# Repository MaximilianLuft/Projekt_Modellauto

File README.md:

# Institutsprojekt 4. Semester #
## Aufbau eines elektrischen Modellautos ##

## FAQ

### What KiCad version to use?
The used template projects are created with KiCad 9.0

### Where to get KiCad?

[kicad.org](https://www.kicad.org/)

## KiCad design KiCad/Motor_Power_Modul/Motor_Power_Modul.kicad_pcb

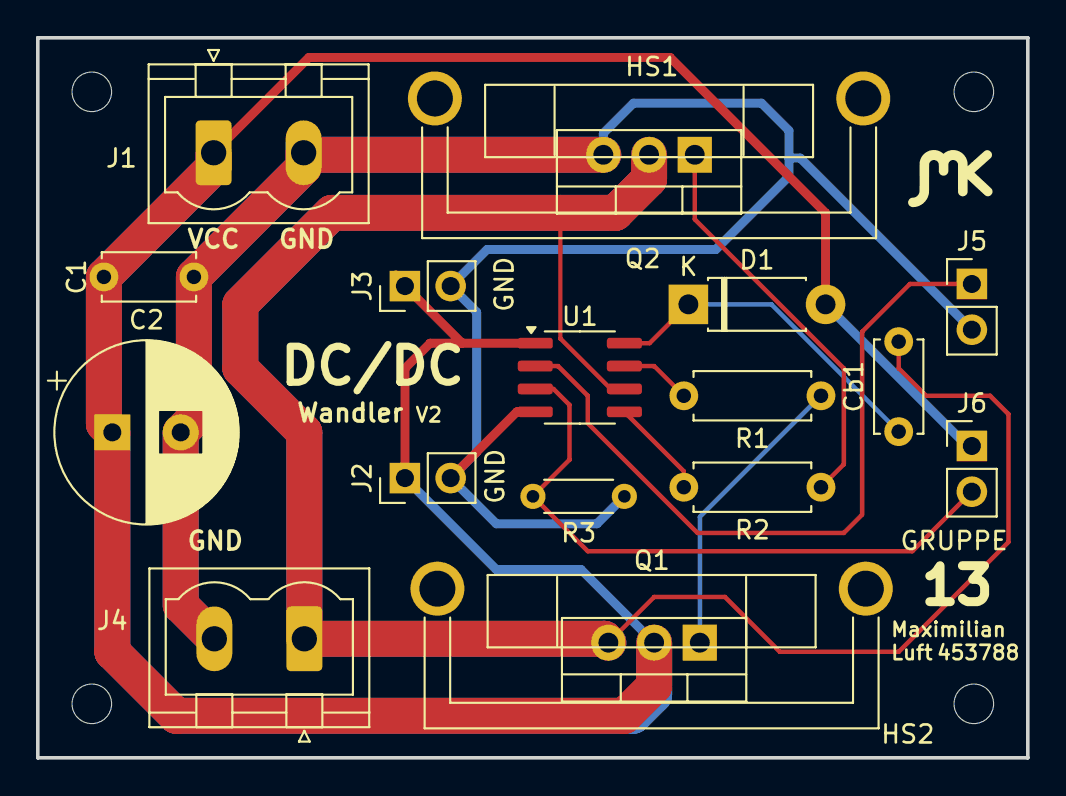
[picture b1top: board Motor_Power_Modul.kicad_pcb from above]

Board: 2 copper layers, 55.0 x 40.0 mm, 22 parts (0 on the bottom side), 9 nets.

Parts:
C1: 100n; C_Disc_D5.0mm_W2.5mm_P5.00mm
C2: 470u; CP_Radial_D10.0mm_P3.80mm
Cb1: 100n; C_Disc_D5.0mm_W2.5mm_P5.00mm
D1: 1N5819; D_DO-41_SOD81_P7.62mm_Horizontal
H1, H2, H3, H4: MountingHole; MountingHole_2.2mm_M2_DIN965
HS1, HS2: Heatsink; Heatsink_Fischer_FK224xx2201_25x8.3mm
J1: Power Input; PhoenixContact_MSTBVA_2,5_2-G_1x02_P5.00mm_Vertical
J2, J3: Power Out; PinHeader_1x02_P2.54mm_Vertical
J4: Motor Output; PhoenixContact_MSTBVA_2,5_2-G_1x02_P5.00mm_Vertical
J5: Input; PinHeader_1x02_P2.54mm_Vertical
J6: Dead Man; PinHeader_1x02_P2.54mm_Vertical
Q1, Q2: IRF3708; TO-220-3_Vertical
R1, R2: 10; R_Axial_DIN0207_L6.3mm_D2.5mm_P7.62mm_Horizontal
R3: 1k; R_Axial_DIN0204_L3.6mm_D1.6mm_P5.08mm_Horizontal
U1: IR2302; SOIC-8_3.9x4.9mm_P1.27mm

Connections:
GND: C1.2, C2.2, J1.2, J2.2, J3.2, J4.2, J5.2, Q2.3 (S), R3.2, U1.4 (COM)
unnamed: Cb1.1, D1.1 (K), U1.8 (VB)
unnamed: Cb1.2, J4.1, Q1.3 (S), Q2.2 (D), U1.6 (VS)
unnamed: J5.1, U1.2 (IN)
unnamed: J6.2, R3.1, U1.3 (~SD)
unnamed: Q1.1 (G), R1.1
unnamed: Q2.1 (G), R2.1
unnamed: R1.2, U1.7 (HO)
VCC: C1.1, C2.1, D1.2 (A), J1.1, J2.1, J3.1, J6.1, Q1.2 (D), U1.1 (VCC)

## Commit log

2025-05-06 1. Iteration DC/DC Wandler
2025-05-10 Iteration 2 von DC/DC Wandler
2025-07-01 neueste Skelett version
2025-07-02 P-Glied fertig, Geschwindigkeitssensor weiterhin mit fehler
2025-07-02 pid arbeit
2025-07-02 PID funktioniert
2025-07-02 Refactor speed_interrupt function to improve speed measurement logic
2025-07-02 Irgendwas test mit post processing aber nicht gut
2025-07-02 Refactor speed_interrupt function to improve timing logic and output speed measurement
2025-07-02 PID motor40
